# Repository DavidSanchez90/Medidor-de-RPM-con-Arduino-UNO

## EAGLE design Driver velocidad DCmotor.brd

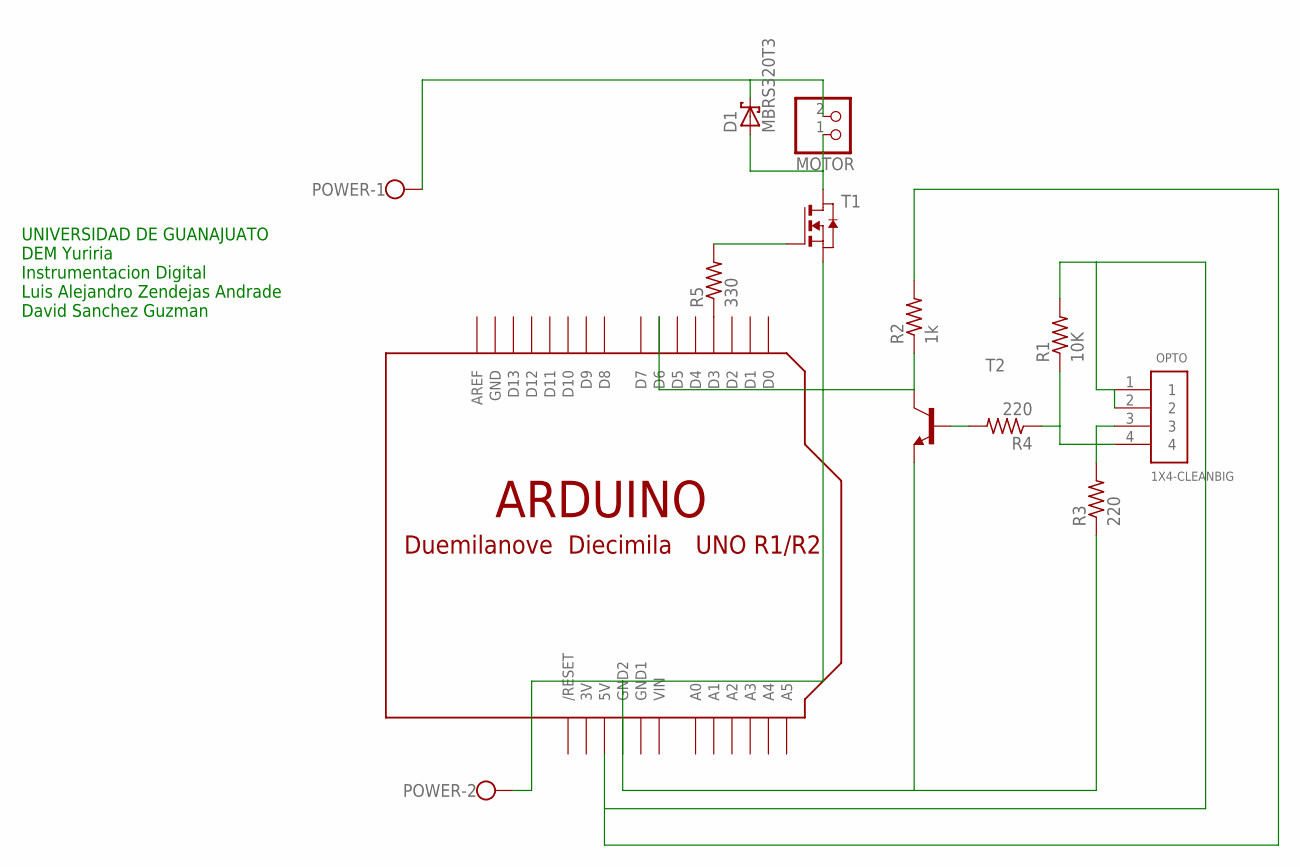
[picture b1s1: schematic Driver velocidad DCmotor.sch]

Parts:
D1: MBRS320T3; SMC
MOTOR: PINHD-1X2; 1X02
OPTO: 1X4-CLEANBIG; 1X04-CLEANBIG
POWER: W237-102
R1: 10K; M1206
R2: 1k; M1206
R3, R4: 220; M1206
R5: 330; M1206
T1: NMOSSOT223; SOT223
T2: BC817-16-NPN-SOT23-BEC; SOT23-BEC
U$1: ARDUINO-NOHOLE

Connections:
3V: U$1.3V
GND: U$1.GND
GND1: U$1.GND1
unnamed: POWER.2, R3.1, T1.3 (S), T2.E, U$1.GND2
unnamed: OPTO.1, OPTO.2, R1.2, R2.2, U$1.5V
unnamed: D1.A, MOTOR.1, T1.2 (D), T1.4 (D)
unnamed: OPTO.4, R1.1, R4.1
unnamed: R4.2, T2.B
unnamed: R2.1, T2.C, U$1.D6
unnamed: OPTO.3, R3.2
unnamed: R5.2, T1.1 (G)
unnamed: D1.C, MOTOR.2, POWER.1
unnamed: R5.1, U$1.D3
VIN: U$1.VIN

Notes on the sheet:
UNIVERSIDAD DE GUANAJUATO DEM Yuriria Instrumentacion Digital Luis Alejandro Zendejas Andrade David Sanchez Guzman

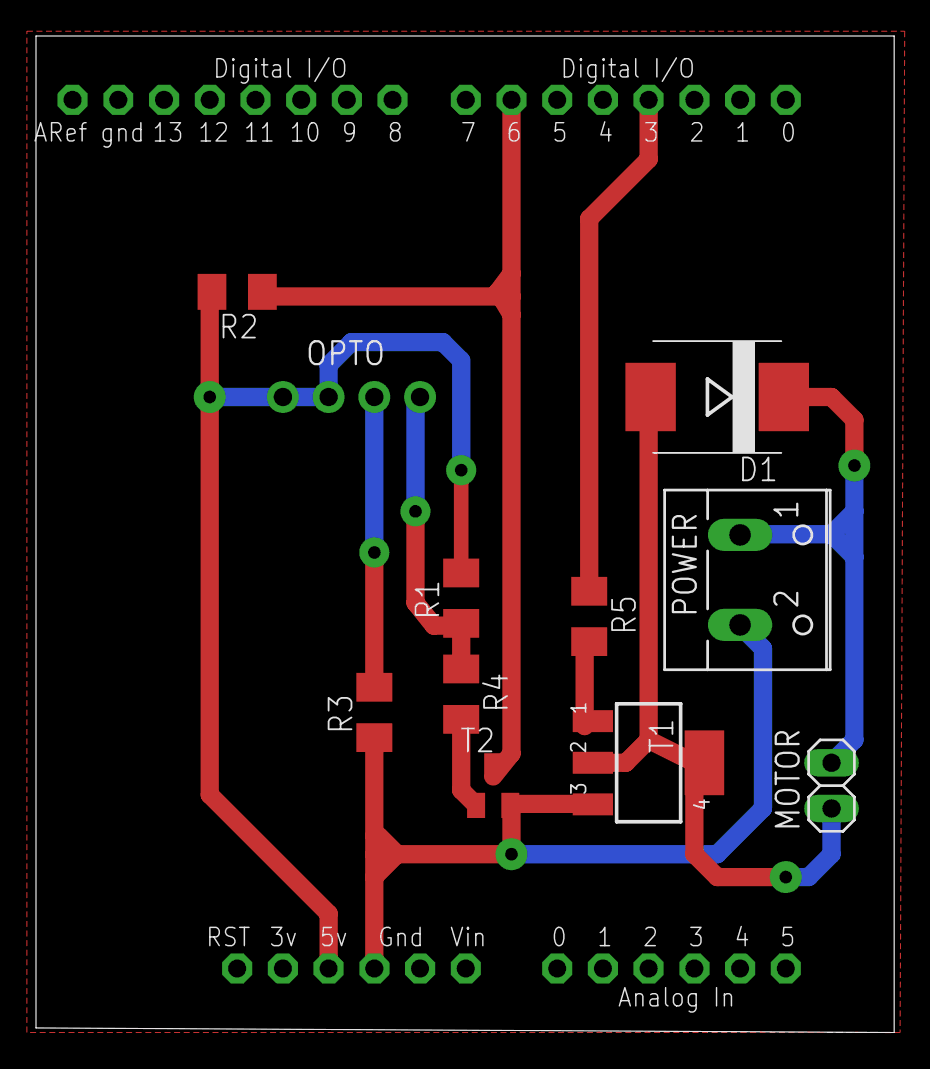
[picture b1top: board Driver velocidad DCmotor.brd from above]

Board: 2 copper layers, 47.7 x 55.4 mm, 12 parts (0 on the bottom side), 10 nets.

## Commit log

2014-11-03 Codigo Arduino Medidor RPM
2014-11-22 PCB
    PCB circuito
2014-11-27 se agrega la resistencia de 330 Ohms a la compuerta del MOSFET
2014-12-01 GUI2
2014-12-01 Osciloscopio en MATlab desde Arduino
2014-12-03 matlab
